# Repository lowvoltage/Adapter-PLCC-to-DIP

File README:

Adapter boards for PLCC sockets

KiCAD schematic and PCB layout by Dimitar Kovachev

Released under the Creative Commons Attribution Share-Alike 3.0 license
http://creativecommons.org/licenses/by-sa/3.0/

Used libraries and 3D models:
http://smisioto.no-ip.org/elettronica/kicad/kicad-en.htm

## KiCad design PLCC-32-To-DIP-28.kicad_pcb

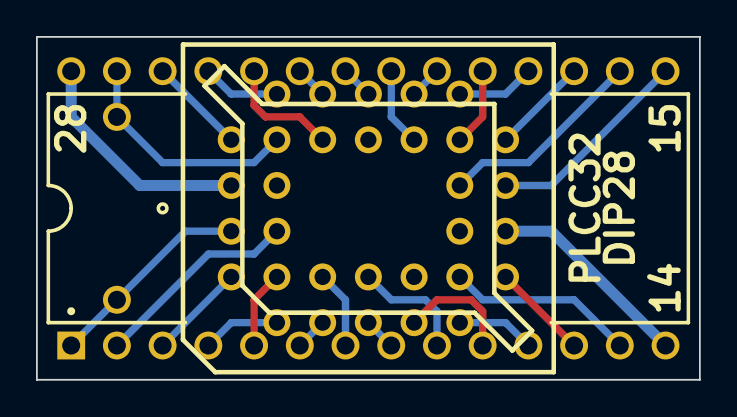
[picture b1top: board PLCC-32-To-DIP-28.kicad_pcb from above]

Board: 2 copper layers, 36.8 x 19.0 mm, 4 parts (0 on the bottom side), 28 nets.

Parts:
1PIN, 1PIN#2: P***; 1pin
U1: 27512; DIP-28__600
U2: 27C512PLCC; plcc32_pth-skt

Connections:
/A0: U1.10, U2.11
/A1: U1.9, U2.10
/A2: U1.8, U2.9
/A3: U1.7, U2.8
/A4: U1.6, U2.7
/A5: U1.5, U2.6
/A6: U1.4, U2.5
/A7: U1.3, U2.4
/A8: U1.25, U2.29
/A9: U1.24, U2.28
/A10: U1.21, U2.24
/A11: U1.23, U2.27
/A12: U1.2, U2.3
/A13: U1.26, U2.30
/A14: 1PIN#2.1, U1.27, U2.31
/A15: 1PIN.1, U1.1, U2.2
/CE: U1.20, U2.23
/D0: U1.11, U2.13
/D1: U1.12, U2.14
/D2: U1.13, U2.15
/D3: U1.15, U2.18
/D4: U1.16, U2.19
/D5: U1.17, U2.20
/D6: U1.18, U2.21
/D7: U1.19, U2.22
/OE: U1.22, U2.25
GND: U1.14, U2.16
VCC: U1.28, U2.32

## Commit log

2013-07-13 Added PLCC-DIP32 adapter
2013-07-14 Fixed gerber settings. Gerber output
